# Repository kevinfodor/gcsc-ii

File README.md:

This is a small embedded controller designed for the purposes of controlling an operating railroad crossing signal with 2 signal lamps and a bell. It was designed to work with a PVC based railroad crossing signal mast approximately 6-feet tall for display, demonstrations and overall amusement. I  have posted this design because I have been contacted by a few others who also saw my railroad crossing project and expressed a desire to build such a signal themselves. I hope this controller will be helpful to anyone who wishes to look at it.

This site contains all of the documentation, source code, schematic and PCB files necessary to build this controller (Rev.B). Please seek the Wiki for more details.

As a secondary goal, I also designed this board to be used as a PIC12 development board. The PCB silkscreen is well documented showing all the pin names and contains lots of holes for jumpers. The board can also be used directly with the PICKit3 programmer from Microchip via the ICSP header. It also has it's own 5V switching power supply on board. So basically all you need to do is provide power and your off and running.

In case your wondering about all the mention of "II" as in GCSC-II, this is a complete re-design of my earlier breadboard attempt found [here on my site](http://www.kevinmfodor.com/home/model-railroading-projects/railroad-crossing-signal). Much has changed since then. This is a very easy to build and very low-cost implementation of that control circuit.

I hope people find this useful. Please feel free to email me or contribute in anyway.

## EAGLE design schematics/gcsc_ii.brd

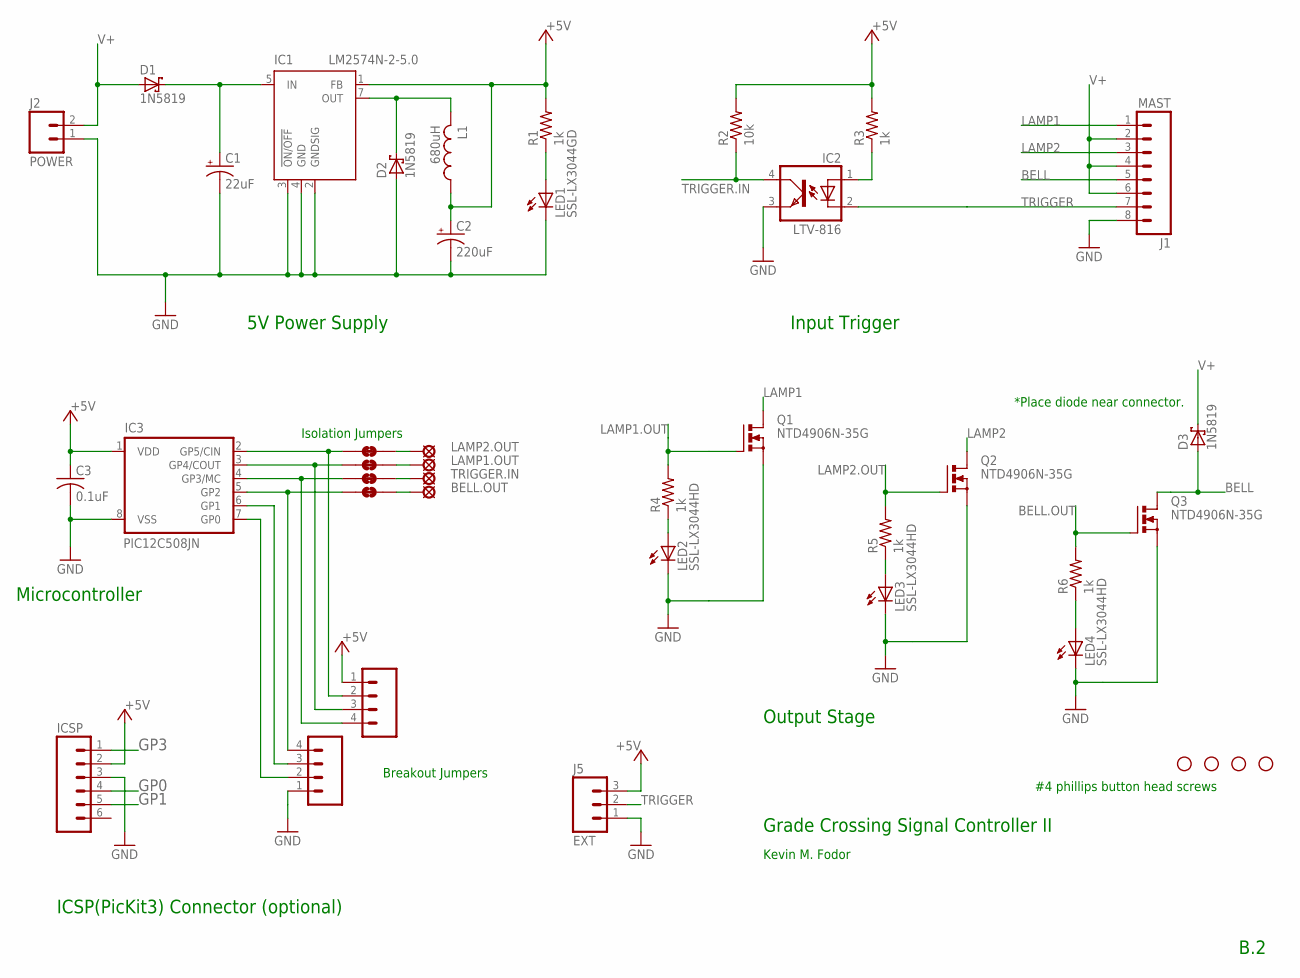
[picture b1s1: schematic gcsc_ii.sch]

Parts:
BELL.OUT: BELL; LSP10; PARTNO 22-28-4012
C1: 22uF; E2-5; PARTNO EEU-FR1H220
C2: 220uF; E2,5-6,3; PARTNO EEU-FR1C221
C3: 0.1uF; C025-024X044; PARTNO 21RZ310-RC
D1, D2, D3: 1N5819; DO41-10; PARTNO 1N5819
GP2: GP2; SJ_2S-TRACE
GP3: GP3; SJ_2S-TRACE
GP4: GP4; SJ_2S-TRACE
GP5: GP5; SJ_2S-TRACE
IC1: LM2574N-2-5.0; DIL8; PARTNO LM2574N-5G
IC2: LTV-816; DIL04; PARTNO LTV-816
IC3: PIC12C508JN; DIL8; MPN PIC12C508-04/P
ICSP: PIC_ICSP_RA; PIC_ICSP; PARTNO 68016-106HLF
J1: MAST; KK-156-8-RA; PARTNO 26-60-5080
J2: POWER; KK-156-2-RA; PARTNO 26-60-5020
J3: IC3_1-4; 1X04_LOCK; PARTNO 22-28-4042
J4: IC3_5-8; 1X04_LOCK; PARTNO 22-28-4042
J5: EXT; MOLEX-1X3_LOCK; PARTNO 22-27-2031
L1: 680uH; RLB0608; PARTNO RLB0608-681KL
LAMP1.OUT: LAMP1; LSP10; PARTNO 22-28-4012
LAMP2.OUT: LAMP2; LSP10; PARTNO 22-28-4012
LED1: SSL-LX3044GD; LED3MM; PARTNO SSL-LX3044GD
LED2, LED3, LED4: SSL-LX3044HD; LED3MM; PARTNO SSL-LX3044HD
Q1, Q2, Q3: NTD4906N-35G; I-PAK_STRAIGHT_LEAD; PARTNO NTD4906N-35G
R1, R3, R4, R5, R6: 1k; 0207/10; PARTNO 299-1K-RC
R2: 10k; 0207/10; PARTNO 299-10K-RC
TRIGGER.IN: TRIGGER; LSP10; PARTNO 22-28-4012
U$1, U$2, U$3, U$4: STAND-OFF

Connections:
+5V: C2.+, C3.1, IC1.1 (FB), IC3.1 (VDD), ICSP.2 (VDD), J3.1, J5.3, L1.1, R1.2, R2.2, R3.2
BELL: D3.A, J1.5, Q3.2 (D)
BELL.OUT: BELL.OUT.MP, GP2.2, Q3.1 (G), R6.2
GND: C1.-, C2.-, C3.2, D2.A, IC1.2 (GNDSIG), IC1.3 (!ON/OFF), IC1.4 (GND), IC2.3 (EMIT), IC3.8 (VSS), ICSP.3 (VSS), J1.8, J2.1, J4.1, J5.1, LED1.K (C), LED2.K (C), LED3.K (C), LED4.K (C), Q1.3 (S), Q2.3 (S), Q3.3 (S)
GP0: IC3.7 (GP0), ICSP.4 (ICSPDAT), J4.2
GP1: IC3.6 (GP1), ICSP.5 (ICSPCLK), J4.3
GP2: GP2.1, IC3.5 (GP2), J4.4
GP3: GP3.1, IC3.4 (GP3/MC), ICSP.1 (!MCLR), J3.4
GP4: GP4.1, IC3.3 (GP4/COUT), J3.3
GP5: GP5.1, IC3.2 (GP5/CIN), J3.2
LAMP1: J1.1, Q1.2 (D)
LAMP1.OUT: GP4.2, LAMP1.OUT.MP, Q1.1 (G), R4.2
LAMP2: J1.3, Q2.2 (D)
LAMP2.OUT: GP5.2, LAMP2.OUT.MP, Q2.1 (G), R5.2
unnamed: IC2.1 (A), R3.1
unnamed: LED1.A, R1.1
unnamed: C1.+, D1.C, IC1.5 (IN)
unnamed: D2.C, IC1.7 (OUT), L1.2
unnamed: LED2.A, R4.1
unnamed: LED3.A, R5.1
unnamed: LED4.A, R6.1
TRIGGER: IC2.2 (C), J1.7, J5.2
TRIGGER.IN: GP3.2, IC2.4 (COL), R2.1, TRIGGER.IN.MP
V+: D1.A, D3.C, J1.2, J1.4, J1.6, J2.2

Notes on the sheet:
#4 phillips button head screws
5V Power Supply
Grade Crossing Signal Controller II
Microcontroller
*Place diode near connector.
Input Trigger
Output Stage
ICSP(PicKit3) Connector (optional)
B.2
Kevin M. Fodor
Breakout Jumpers
Isolation Jumpers

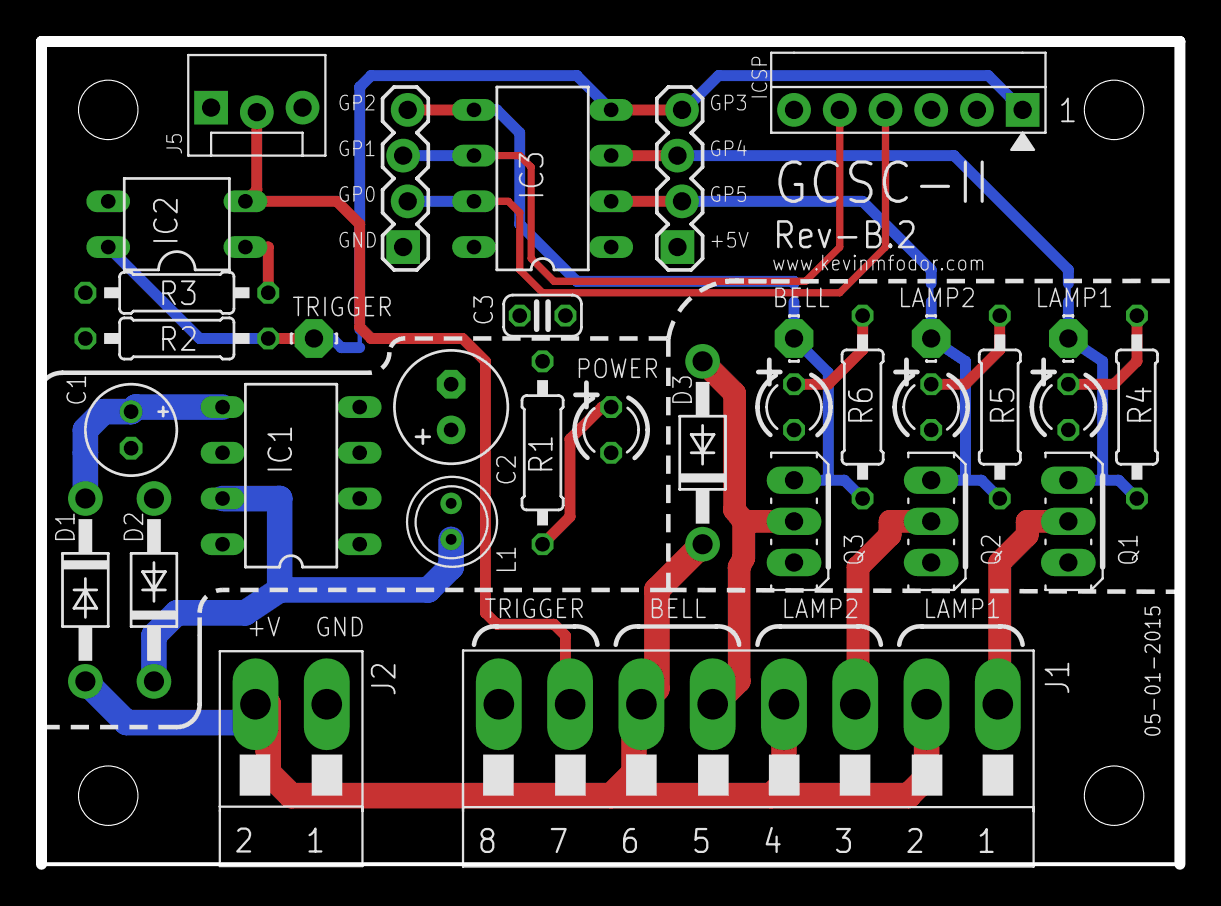
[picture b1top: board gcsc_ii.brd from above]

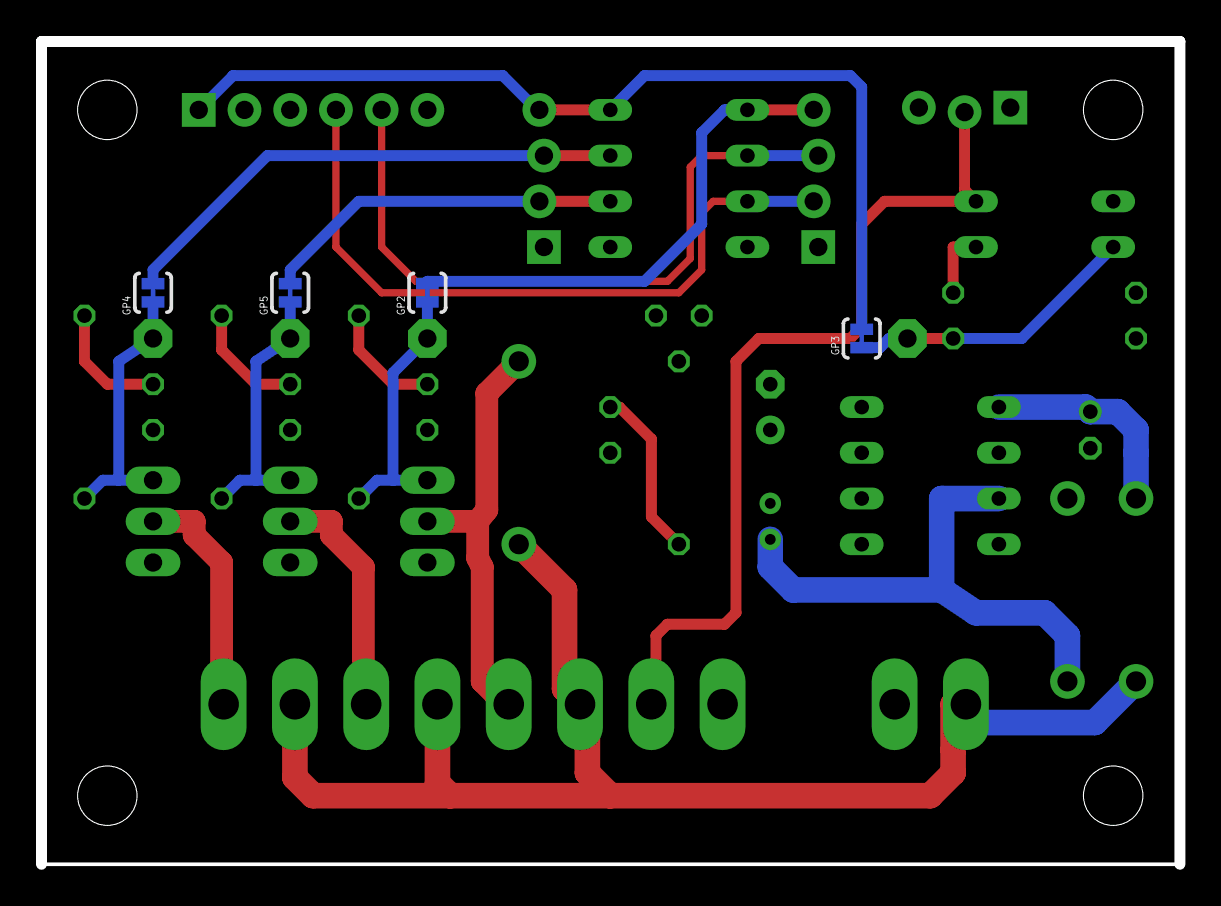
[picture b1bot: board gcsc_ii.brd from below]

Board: 2 copper layers, 63.2 x 45.7 mm, 41 parts (4 on the bottom side), 24 nets.

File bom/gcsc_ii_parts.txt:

Partlist

Exported from gcsc_ii.sch at 5/1/2012 7:53:26 AM

EAGLE Version 6.2.0 Copyright (c) 1988-2012 CadSoft

Assembly variant: 

Part       Value          Device             Package             Library  Sheet

BELL.OUT   BELL           LSP10              LSP10               kevin    1
C1         22uF           CPOL-USFR-5        E2-5                kevin    1
C2         220uF          CPOL-USFR-6,3      E2,5-6,3            kevin    1
C3         0.1uF          C-USC025-024X044   C025-024X044        kevin    1
D1         1N5819         SCHOTTKY-DIODEDO41 DO41-10             kevin    1
D2         1N5819         SCHOTTKY-DIODEDO41 DO41-10             kevin    1
D3         1N5819         SCHOTTKY-DIODEDO41 DO41-10             kevin    1
GP2        GP2            SJ_CLOSED          SJ_2S-TRACE         kevin    1
GP3        GP3            SJ_CLOSED          SJ_2S-TRACE         kevin    1
GP4        GP4            SJ_CLOSED          SJ_2S-TRACE         kevin    1
GP5        GP5            SJ_CLOSED          SJ_2S-TRACE         kevin    1
IC1        LM2574N-2-5.0  LM2574N-2-5.0      DIL8                kevin    1
IC2        LTV-816        LTV816             DIL04               kevin    1
IC3        PIC12C508JN    PIC12C508JN        DIL8                kevin    1
ICSP       PIC_ICSP_RA    PIC_ICSP_RA        PIC_ICSP            kevin    1
J1         MAST           KK-156-8-RA        KK-156-8-RA         kevin    1
J2         POWER          KK-156-2RA         KK-156-2-RA         kevin    1
J3         IC3_1-4        M04LOCK            1X04_LOCK           kevin    1
J4         IC3_5-8        M04LOCK            1X04_LOCK           kevin    1
J5         EXT            M03POLAR_LOCK      MOLEX-1X3_LOCK      kevin    1
L1         680uH          RLB0608            RLB0608             kevin    1
LAMP1.OUT  LAMP1          LSP10              LSP10               kevin    1
LAMP2.OUT  LAMP2          LSP10              LSP10               kevin    1
LED1       SSL-LX3044GD   LED3MM             LED3MM              kevin    1
LED2       SSL-LX3044HD   LED3MM             LED3MM              kevin    1
LED3       SSL-LX3044HD   LED3MM             LED3MM              kevin    1
LED4       SSL-LX3044HD   LED3MM             LED3MM              kevin    1
Q1         NTD4906N-35G   NTD4906N           I-PAK_STRAIGHT_LEAD kevin    1
Q2         NTD4906N-35G   NTD4906N           I-PAK_STRAIGHT_LEAD kevin    1
Q3         NTD4906N-35G   NTD4906N           I-PAK_STRAIGHT_LEAD kevin    1
R1         1k             R-US0207/10        0207/10             kevin    1
R2         10k            R-US0207/10        0207/10             kevin    1
R3         1k             R-US0207/10        0207/10             kevin    1
R4         1k             R-US0207/10        0207/10             kevin    1
R5         1k             R-US0207/10        0207/10             kevin    1
R6         1k             R-US0207/10        0207/10             kevin    1
TRIGGER.IN TRIGGER        LSP10              LSP10               kevin    1

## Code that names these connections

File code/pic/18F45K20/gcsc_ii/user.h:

/******************************************************************************/
/* User Level #define Macros                                                  */
/******************************************************************************/

/* TODO Application specific user parameters used in user.c may go here */

/******************************************************************************/
/* User Function Prototypes                                                   */
/******************************************************************************/

/* TODO User level functions prototypes (i.e. InitApp) go here */

#if _18F45K20 == 1

// Definitions for outputs (lamps, bell)
#define LAMP1       (0b00000001) // RD0
#define LAMP2       (0b00000010) // RD1
#define BELL        (0b00000100) // RD2
#define HEARTBEAT   (0b00001000) // RD3
#define PORT (LATD)

// Definitions for inputs
#define TRIGGER (PORTBbits.RB0 ? 0 : 1)

// Definitions for clock timer and delay
#define FOSC (31250)
#define TMR0_CLOCK_TICK_USEC ((4 * USEC_PER_SEC) / FOSC) // 128 usec
#define TMR0_COUNT (256 - (TMR0_TIMEOUT_USEC / TMR0_CLOCK_TICK_USEC)) // 178
#define USEC_PER_TICK ((256 - TMR0_COUNT) * TMR0_CLOCK_TICK_USEC) // 9984

#define TIMER_EXPIRED (INTCONbits.TMR0IF)
#define TIMER_RESET (TMR0L = TMR0_COUNT);INTCONbits.TMR0IF = 0

#else

#error Sorry! Incorrect header used for target chip.

#endif

void InitApp(void);         /* I/O and Peripheral Initialization */

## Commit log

2012-07-11 Initial files
2012-07-17 a simple variation with only on/off control. Disables long-press.
2012-07-17 Modified gitignore
2012-07-18 Add new background images
2012-07-19 Updated design doc and exported to PDF
2012-07-27 Added Make:Projects guide which explains how to build this PCB.
2013-08-11 Updated per latest MPLAB-X
2013-08-23 Cleaned-up silk screen and some minor clean-up to traces.
2013-08-28 Cleaned-up silkscreen, thickened traces. Electrically design is unaltered
2013-09-07 Updated project files to support latest version of MPLAB-X. No code changes made.
2013-09-09 Updated PCB to Rev B.1 No changes to parts or design. Only some cleaning up of traces (thickening) and cosmetic improvements
2013-11-04 Rebuilt
2015-04-09 ./finishGoogleCodeGitHubWikiMigration_mod2: Moved ProjectHome.md from wiki branch to README.md in master branch.
2015-05-03 Updated state machine to support configurable timeouts for lamps, bell and overall run duration of each. Modified state machine to handle a faster and independent bell rate
2015-05-03 Made slight modification to the top-silk to add heavier font for the "+" markings on the LEDs. Also updated to Eagle 6.6.0. Regenerated gerbers, schematic and archive.
